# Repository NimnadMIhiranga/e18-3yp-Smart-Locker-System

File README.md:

___
# Smart Locker System
___

These days we have heard some cases of stolen bags and laptops of engineering faculty students inside the engineering faculty. It happens mostly when students go to the library or laboratories. Because when they must go to those places, they should leave their bag outside. But there aren’t enough facilities to confirm the protection of their bags and laptops. So as a solution, we will develop an intelligent locker system for those places.

There are some lockers to put our bags in those places, but they need more safety. So, considering our locker system, a considerable number of lockers relate to the mobile application. Students can book a locker using the application, but the booking will only be available for 30 minutes. To unlock a locker, students should select the locker number and open it using the mobile application and fingerprint system. After getting the bag also, students should lock the vault. If a student needs to remember to get full bags from the locker, there will be an indicator indicating that the student is not allowed to lock it when remaining some bags. The system will include a rechargeable battery as a power backup to tolerate the effects of power cuts.

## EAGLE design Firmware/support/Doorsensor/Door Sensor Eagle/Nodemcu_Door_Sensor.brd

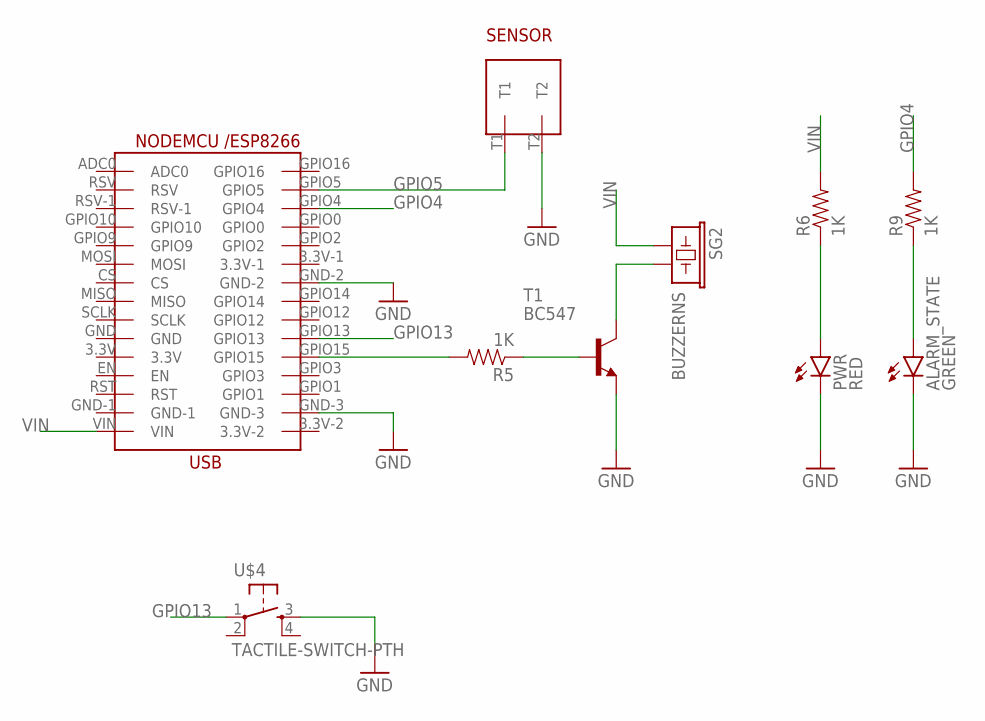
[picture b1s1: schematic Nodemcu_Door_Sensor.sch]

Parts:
ALARM_STATE: GREEN; LED3MM
PWR: RED; LED3MM
R5, R6, R9: 1K; AXIAL-0.4
SENSOR: TER_CON_2PIN_ROINCOPTH; TER_CON_2PIN_ROINCO
SG2: BUZZERNS; BUZZER-12MM-NS
T1: BC547; TO92
U$1: ROINCO_NODEMCU_ESP8266
U$4: TACTILE-SWITCH-PTH; TAC-SWITCH-PTH

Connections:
GND: ALARM_STATE.K (C), PWR.K (C), SENSOR.T2, T1.1 (E), U$1.GND-2, U$1.GND-3, U$4.3
GPIO4: R9.P$2 (2), U$1.GPIO4
GPIO5: SENSOR.T1, U$1.GPIO5
GPIO13: U$1.GPIO13, U$4.1
unnamed: R5.P$2 (2), U$1.GPIO15
unnamed: R5.P$1 (1), T1.2 (B)
unnamed: SG2.- (2), T1.3 (C)
unnamed: PWR.A, R6.P$1 (1)
unnamed: ALARM_STATE.A, R9.P$1 (1)
VIN: R6.P$2 (2), SG2.+ (1), U$1.VIN

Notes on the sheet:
SENSOR

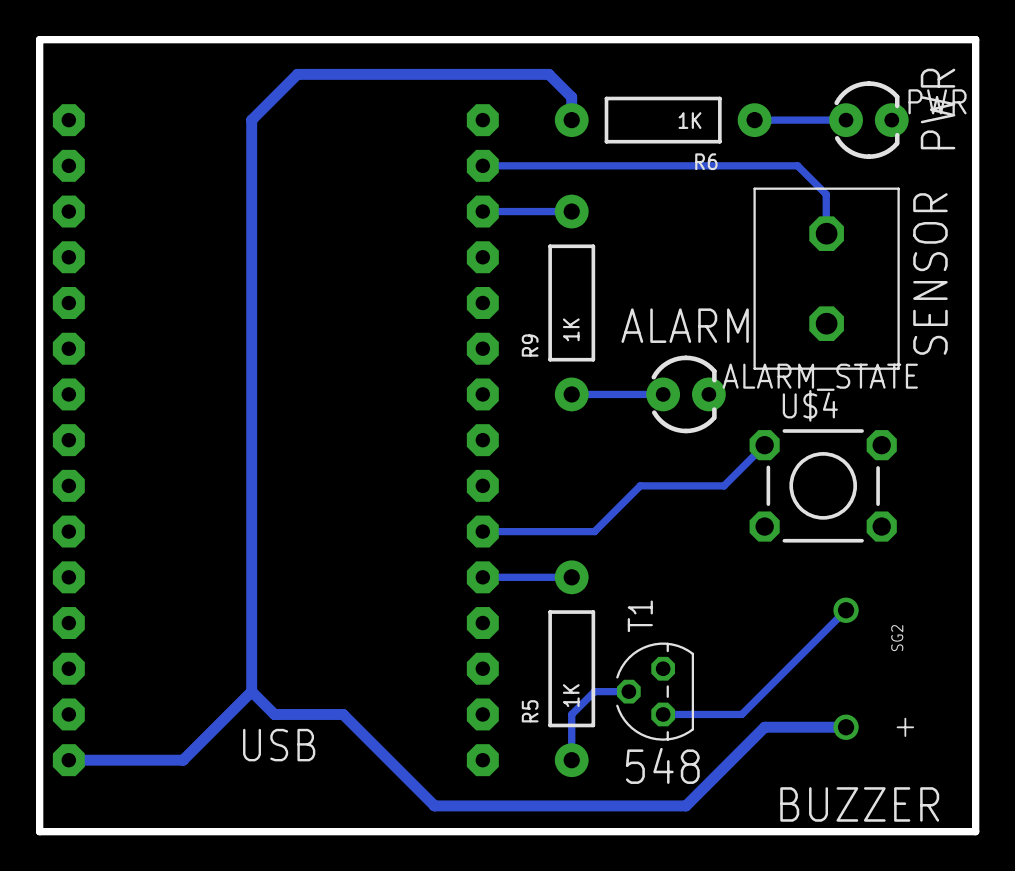
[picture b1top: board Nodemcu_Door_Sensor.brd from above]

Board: 2 copper layers, 52.0 x 44.0 mm, 10 parts (0 on the bottom side), 10 nets.

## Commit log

2022-11-02 Added the json file
2022-11-16 initial web pages and app login
2022-11-27 changes in UI and initial Homeview implemented
2022-11-27 Project pages updated
2022-11-28 Created the animated video
2022-11-28 Created the user regsitration and user login web interface
2022-11-28 Updated the project page
2022-12-03 email verififcation implemented
2022-12-07 Password reset implemented
2022-12-10 floating button and navigation to new window
2022-12-10 location view implemented and add reservation view started
2022-12-14 Created welcome page
2022-12-14 Added welcome page
2022-12-14 nothing
2022-12-14 added the slocker logo
2022-12-14 welcome page
2022-12-15 Time picker added for reservation page
2022-12-16 Signup page added
2022-12-16 Signin page added
2022-12-16 3D models and Reservations Backend in App
2022-12-16 Adding user dashboard page
2022-12-16 initial reservation view implemented
2022-12-16 Intergration tests for applogin
2022-12-16 added the initial signup page
2022-12-17 Setting firebase authentication
2022-12-17 firebase authentication
2022-12-19 completed signup to firebase
2022-12-19 completed sign into firebase
2022-12-20 deleting reservations
2022-12-20 changes in home view
2022-12-20 updated the signup page
2022-12-20 creating locker adding
2022-12-20 bug fix
2022-12-20 connected single esp8266 to app for demonstration
2022-12-20 Created the Locker room and addlocker page
2022-12-20 web page updated
2022-12-20 Location list view created
2022-12-21 Created user admin authentication
2022-12-21 pages updated
2022-12-21 pages
2022-12-21 solve the image not showing bug in the project page
2022-12-30 change password
2022-12-30 add location via dialog box
2022-12-30 locker delete and edit
2022-12-30 location edit and delete
2022-12-31 locker page created
2023-01-04 locker adding
2023-01-04 updated the dashboard page
2023-01-04 firmware added
2023-01-05 Admin signup
2023-01-06 add lockers into realtime database
2023-01-06 locker path added
2023-01-06 added the wifi checkup function
2023-01-07 updated the project page and the frontend
2023-01-07 app implemeted with support for realtime database
2023-01-08 lcd menu base code implemented
2023-01-08 menu implmented with back function
2023-01-08 Lockers list view
2023-01-10 getting pin from user
2023-01-10 full delete and backspace for pin implemented
2023-01-10 PIN compare implemeneted
2023-01-11 Locker setting
2023-01-11 Locker parameters
2023-01-12 fingerprint check add for menu
2023-01-12 door sensor folder added
2023-01-12 wifi check added
2023-01-12 Keypad check added
2023-01-12 added fingerprint sensor check
2023-01-12 fingerprint enroll can done through menu
2023-01-12 can rreturn to main function while registering a finger
2023-01-12 booking.js created
2023-01-12 debugged
2023-01-13 Booking list and Bokking canceling function
2023-01-14 implemented history and reservation things (RD)
2023-01-14 added firebase connection to the mcu
2023-01-14 door sensor
2023-01-14 added the path to door sensor state and reduced the latency to update in the database
2023-01-14 integrated the component check and the door sensor to the final code
2023-01-14 debugging
2023-01-15 UI and functions
2023-01-15 abject check using ultra zonic
2023-01-15 integrated the component check and door sensor check
2023-01-15 UI changes
2023-01-15 small changes
2023-01-15 object check state to firebase and buzzer code
2023-01-15 Cancel reservation automatically implemented
2023-01-15 changes in app
2023-01-16 added the component check to the loop funtion
2023-01-16 add fingerprint functions to the final code
2023-01-16 update the final code
2023-01-16 made the flow of initial usage of the slocker
2023-01-16 UI designs and limit pin to 4 digits
2023-01-16 added the initial finger enrolment logic
2023-01-17 added logic and the lcd fn for when locker is not booked
2023-01-17 bug fixes
2023-01-18 web final
2023-01-22 docs
2023-01-22 application demo vedio added
2023-01-22 added the demonstration video
2023-01-22 added the web app demo

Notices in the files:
parts and their libraries:
SparkFun-Resistors: Licensing: Creative Commons ShareAlike 4.0 International - https://creativecommons.org/licenses/by-sa/4.0
